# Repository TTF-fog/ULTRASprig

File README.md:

# the ULTRASprig

an updated version of the [Sprig](https://github.com/hackclub/sprig/), made to be ultra-modular and expansible!

# Why?
the current model of the sprig is a bit... outdated. It still runs on the RP2040, has only 4 (broken out) gpios and just 2Mb of flash. The ULTRASprig has 7 usable GPIOs, and a completely new expansion system that allows for up to 16MB of additional flash, + PSRAM. it also uses I2C "modules" to give even more  interfaces

## Notes:
- KiCad will throw a DRC error for the placement of the mounting headers (courtyard overlap with display), but this can be ignored safely 

# Setup
## RP2354B
- get the larger packages (the BQ, RP2354, and the TP) pre-assembled
- use a stencil to solder the smaller passives
- solder male headers into the broken out pins
## Mainboard
- Solder all components except the pinsockets
- while soldering the pinsockets, make sure to have 1mm of clearance between the tips and the SPI display
- insert the SD Card into the SPI Display
- for the battery headers, one battery header will be connected to the + and - of the battery, and the other should be connected to the battery pins of the coreboard
## Case
- the case must be printed in two parts, the front and the back
- there are 4 mounting holes in the case, which must be connected using screws to those mounting holes on the mainboard
- after that, place the backplate, ensuring that the battery pins line up with the battery hoels
# Usage
- build the firmware and flash it on the sprig

# Sub(Links)
- [Zine](Sprig_Zine.pdf)
- Mainboard
    - [Mainboard BoM](BOM.csv)
    - [Gerbers - Mainboard](gerbers.zip)
    - [Mainboard Design](Mainboard/)
- Core Board
    - [Core BoM](core_board/RP2354B/BOM.csv)
    - [Coreboard Design Files](core_board/RP2354B/)
- Expansions
    - IO Expander   
        - [Design](Expansions/IOExpander/)
        - [Gerbers](Expansions/IOExpander/Gerbers.zip)
        - [BoM](Expansions/IOExpander/BOM.csv)
    - Flash Breakout   
        - [Design](Expansions/FlashBreakout/)
        - [Gerbers](Expansions/FlashBreakout/gerbers.zip)
        - [BoM](Expansions/FlashBreakout/BOM.csv)
    - IMU Breakout   
        - [Design](Expansions/IMUBreakout/)
        - [Gerbers](Expansions/IMUBreakout/Gerbers.zip)
        - [BoM](Expansions/IMUBreakout/BOM.csv)

- [Gerbers - coreboard](core_board/RP2354B/Gerbers.zip)

# Zine

> check the pdf version too!
# Renders

> front view

> back view w/ board and battery headers

> front view, main board with modules

> a very rushed blender render rhyme

> case for the ULTRASprig

> textured preview of CAD
# Routing

> routed mainboard

> routed coreboard

# Schematics

> mainboard schematic

> coreboard schematic

> note: some of the cad model pictures are outdated, double-check the source file

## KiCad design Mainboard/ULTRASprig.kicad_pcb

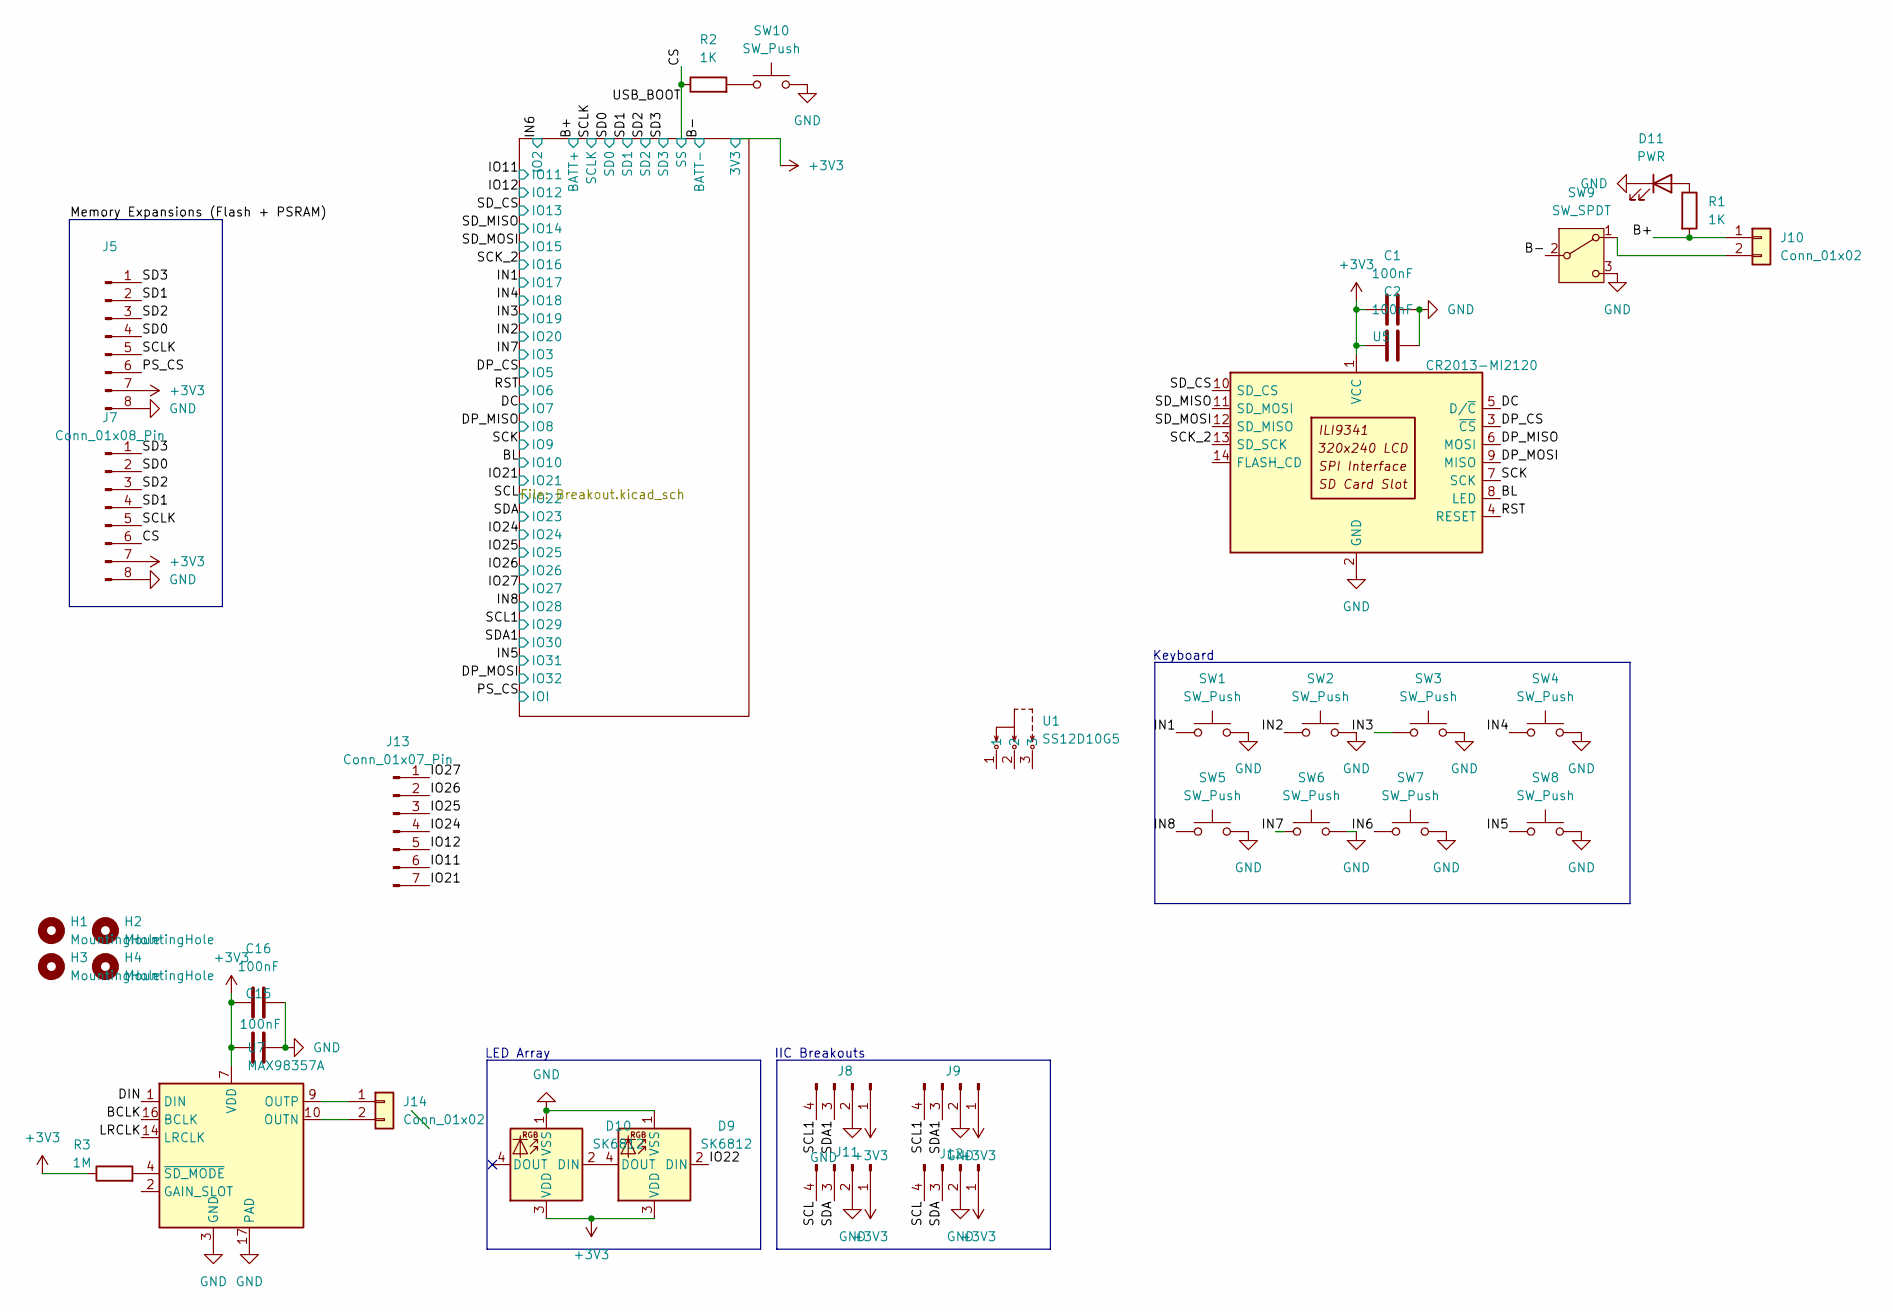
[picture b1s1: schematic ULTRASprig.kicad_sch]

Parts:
C1, C2, C15, C16: 100nF; C_0402_1005Metric
D9, D10: SK6812; LED_SK6812_PLCC4_5.0x5.0mm_P3.2mm
D11: PWR; LED_0603_1608Metric
H1, H2, H3, H4: MountingHole; MountingHole_2.2mm_M2
J5, J7: Conn_01x08_Pin; PinSocket_1x08_P2.54mm_Horizontal
J8, J9, J11, J12: Conn_01x04_Pin; PinSocket_1x04_P2.54mm_Horizontal
J10, J14: Conn_01x02; PinHeader_1x02_P2.54mm_Vertical
J13: Conn_01x07_Pin; PinSocket_1x07_P2.54mm_Vertical
R1: 1K; R_0402_1005Metric
R2: 1K; R_0603_1608Metric
R3: 1M; R_0603_1608Metric
SW1, SW2, SW3, SW4, SW5, SW6, SW7, SW8: SW_Push; SW_PUSH-12mm
SW9: SW_SPDT; SW_SPST_B3S-1100
SW10: SW_Push; SW_Push_1P1T_NO_CK_KMR2
U1: SS12D10G5; SW-TH_SHOU-HAN_SS12D10G4; MPN SS12D10G5; LCSC Part C7431054
U5: CR2013-MI2120
U7: MAX98357A; TQFN-16-1EP_3x3mm_P0.5mm_EP1.23x1.23mm

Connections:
+3V3: C1.1, C2.1, C15.2, C16.2, D9.3 (VDD), D10.3 (VDD), J5.7, J7.7, J8.1, J9.1, J11.1, J12.1, R3.1, U5.1 (VCC), U7.7 (VDD), U7.8 (VDD); also elsewhere on the board
/B+: J10.1, R1.2; also elsewhere on the board
/B-: SW9.2 (B); also elsewhere on the board
/BCLK: U7.16 (BCLK)
/BL: U5.8 (LED); also elsewhere on the board
/CS: J7.6, R2.1; also elsewhere on the board
/DC: U5.5 (D/~C); also elsewhere on the board
/DIN: U7.1 (DIN)
/DP_CS: U5.3 (~CS); also elsewhere on the board
/DP_MISO: U5.6 (MOSI); also elsewhere on the board
/DP_MOSI: U5.9 (MISO); also elsewhere on the board
/IN1: SW1.1; also elsewhere on the board
/IN2: SW2.1; also elsewhere on the board
/IN3: SW3.1; also elsewhere on the board
/IN4: SW4.1; also elsewhere on the board
/IN5: SW8.1; also elsewhere on the board
/IN6: SW7.1; also elsewhere on the board
/IN7: SW6.1; also elsewhere on the board
/IN8: SW5.1; also elsewhere on the board
/IO11: J13.6; also elsewhere on the board
/IO12: J13.5; also elsewhere on the board
/IO21: J13.7; also elsewhere on the board
/IO22: D9.2 (DIN)
/IO24: J13.4; also elsewhere on the board
/IO25: J13.3; also elsewhere on the board
/IO26: J13.2; also elsewhere on the board
/IO27: J13.1; also elsewhere on the board
/LRCLK: U7.14 (LRCLK)
/PS_CS: J5.6; also elsewhere on the board
/RST: U5.4 (RESET); also elsewhere on the board
/SCK: U5.7 (SCK); also elsewhere on the board
/SCK_2: U5.13 (SD_SCK); also elsewhere on the board
/SCL: J11.4, J12.4; also elsewhere on the board
/SCL1: J8.4, J9.4; also elsewhere on the board
/SCLK: J5.5, J7.5; also elsewhere on the board
/SD0: J5.4, J7.2; also elsewhere on the board
/SD1: J5.2, J7.4; also elsewhere on the board
/SD2: J5.3, J7.3; also elsewhere on the board
/SD3: J5.1, J7.1; also elsewhere on the board
/SDA: J11.3, J12.3; also elsewhere on the board
/SDA1: J8.3, J9.3; also elsewhere on the board
/SD_CS: U5.10 (SD_CS); also elsewhere on the board
/SD_MISO: U5.11 (SD_MOSI); also elsewhere on the board
/SD_MOSI: U5.12 (SD_MISO); also elsewhere on the board
GND: C1.2, C2.2, C15.1, C16.1, D9.1 (VSS), D10.1 (VSS), D11.1 (K), J5.8, J7.8, J8.2, J9.2, J11.2, J12.2, SW1.2, SW2.2, SW3.2, SW4.2, SW5.2, SW6.2, SW7.2, SW8.2, SW9.3 (C), SW10.2, U5.2 (GND), U7.3 (GND), U7.11 (GND), U7.15 (GND), U7.17 (PAD)
unnamed: D9.4 (DOUT), D10.2 (DIN)
unnamed: D11.2 (A), R1.1
unnamed: J10.2, SW9.1 (A)
unnamed: J14.1, U7.9 (OUTP)
unnamed: J14.2, U7.10 (OUTN)
unnamed: R2.2, SW10.1
unnamed: R3.2, U7.4 (~SD_MODE)

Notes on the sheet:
Keyboard
LED Array
IIC Breakouts

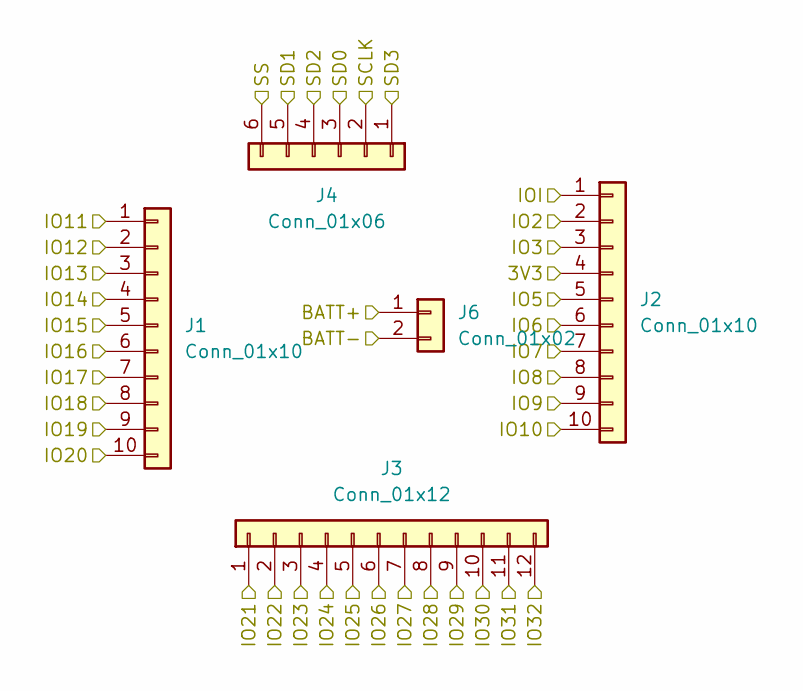
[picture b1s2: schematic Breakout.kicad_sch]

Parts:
J1, J2: Conn_01x10; PinSocket_1x10_P2.54mm_Vertical
J3: Conn_01x12; PinSocket_1x12_P2.54mm_Vertical
J4: Conn_01x06; PinSocket_1x06_P2.54mm_Vertical
J6: Conn_01x02; PinHeader_1x02_P2.54mm_Vertical

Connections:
+3V3: J2.4; also elsewhere on the board
/B+: J6.1; also elsewhere on the board
/B-: J6.2; also elsewhere on the board
/BL: J2.10; also elsewhere on the board
/CS: J4.6; also elsewhere on the board
/DC: J2.7; also elsewhere on the board
/DP_CS: J2.5; also elsewhere on the board
/DP_MISO: J2.8; also elsewhere on the board
/DP_MOSI: J3.12; also elsewhere on the board
/IN1: J1.7; also elsewhere on the board
/IN2: J1.10; also elsewhere on the board
/IN3: J1.9; also elsewhere on the board
/IN4: J1.8; also elsewhere on the board
/IN5: J3.11; also elsewhere on the board
/IN6: J2.2; also elsewhere on the board
/IN7: J2.3; also elsewhere on the board
/IN8: J3.8; also elsewhere on the board
/IO11: J1.1; also elsewhere on the board
/IO12: J1.2; also elsewhere on the board
/IO21: J3.1; also elsewhere on the board
/IO24: J3.4; also elsewhere on the board
/IO25: J3.5; also elsewhere on the board
/IO26: J3.6; also elsewhere on the board
/IO27: J3.7; also elsewhere on the board
/PS_CS: J2.1; also elsewhere on the board
/RST: J2.6; also elsewhere on the board
/SCK: J2.9; also elsewhere on the board
/SCK_2: J1.6; also elsewhere on the board
/SCL: J3.2; also elsewhere on the board
/SCL1: J3.9; also elsewhere on the board
/SCLK: J4.2; also elsewhere on the board
/SD0: J4.3; also elsewhere on the board
/SD1: J4.5; also elsewhere on the board
/SD2: J4.4; also elsewhere on the board
/SD3: J4.1; also elsewhere on the board
/SDA: J3.3; also elsewhere on the board
/SDA1: J3.10; also elsewhere on the board
/SD_CS: J1.3; also elsewhere on the board
/SD_MISO: J1.4; also elsewhere on the board
/SD_MOSI: J1.5; also elsewhere on the board

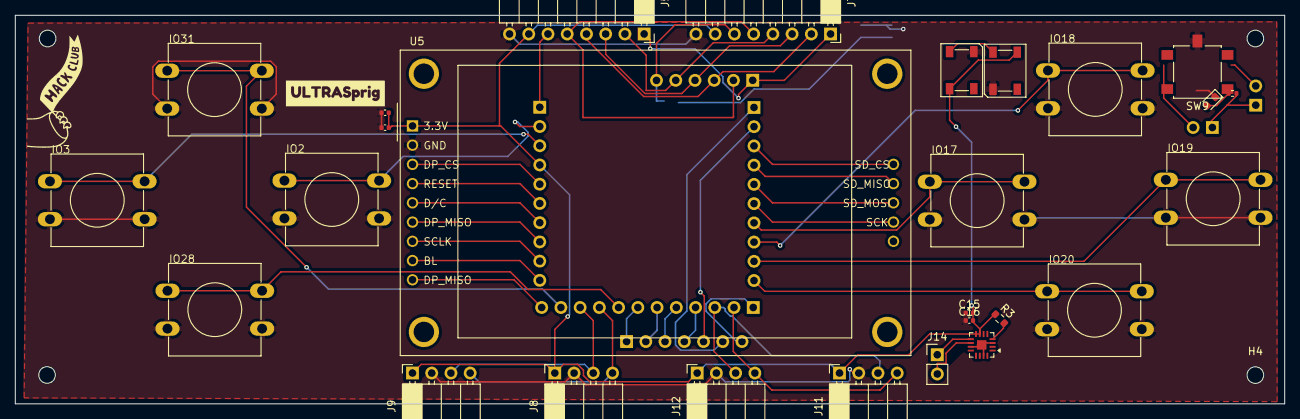
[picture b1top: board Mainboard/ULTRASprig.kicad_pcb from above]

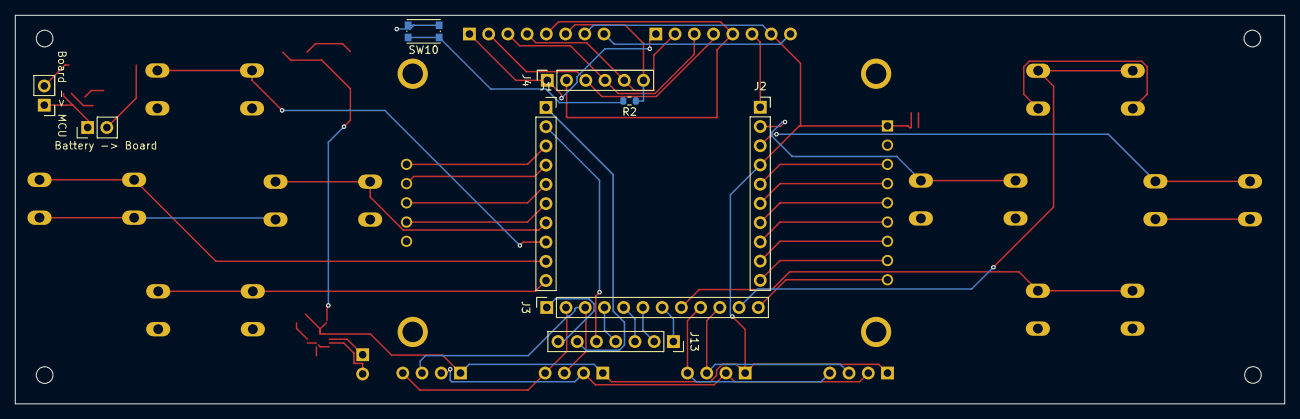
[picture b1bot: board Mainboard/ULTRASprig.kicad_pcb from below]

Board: 2 copper layers, 167.6 x 51.3 mm, 41 parts (9 on the bottom side), 48 nets.

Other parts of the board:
kibuzzard-6A30251C: G***; kibuzzard-6A30251C

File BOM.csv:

Comment,Designator,Footprint,LCSC,Quantity,URL, Unit Price,Price
100nF,"C1,C15,C16,C2",C_0402_1005Metric,C1525,4,https://www.lcsc.com/product-detail/C1525.html ,0.0031,0.31
1K,R1,R_0402_1005Metric,C11702,1,https://www.lcsc.com/product-detail/C11702.html ,0.0011,0.011
1K,R2,R_0603_1608Metric,C21190,1,https://www.lcsc.com/product-detail/C21190.html ,0.0017,0.017
1M,R3,R_0603_1608Metric,C22935,1,https://www.lcsc.com/product-detail/C22935.html,0.0018,0.18
Conn_01x02,"J10,J6",PinHeader_1x02_P2.54mm_Vertical,C492401,2,https://www.lcsc.com/product-detail/C492401.html,0.0161,0.81
Conn_01x04_Pin,"J11,J12,J8,J9",PinSocket_1x04_P2.54mm_Horizontal,C2718488,4,https://www.lcsc.com/product-detail/C2718488.html,0.0786,0.79
Conn_01x06,J4,PinSocket_1x06_P2.54mm_Vertical,C7499363,1,https://www.lcsc.com/product-detail/C7499363.html,0.1286,0.64
Conn_01x07_Pin,J13,PinSocket_1x07_P2.54mm_Vertical,C5371993,1,https://www.lcsc.com/product-detail/C5371993.html,0.0963,0.48
Conn_01x08_Pin,"J5,J7",PinSocket_1x08_P2.54mm_Horizontal,C7499328,2,https://www.lcsc.com/product-detail/C7499328.html,0.1351,0.68
Conn_01x10,"J1,J2",PinSocket_1x10_P2.54mm_Vertical,C2925557,2,https://www.lcsc.com/product-detail/C2925557.html,0.1279,0.64
Conn_01x12,J3,PinSocket_1x12_P2.54mm_Vertical,C492401,1,https://www.lcsc.com/product-detail/C492401.html,0.0161,0.81
MAX98357A,U7,TQFN-16-1EP_3x3mm_P0.5mm_EP1.23x1.23mm,C910544,1,https://www.lcsc.com/product-detail/C910544.html,1.3362,1.34
PWR,D11,LED_0603_1608Metric,C2286,1,https://www.lcsc.com/product-detail/C2286.html,0.0073,0.73
SK6812,"D10,D9",LED_SK6812_PLCC4_5.0x5.0mm_P3.2mm,C5378734,2,https://www.lcsc.com/product-detail/C5378734.html,0.1656,0.83
SW_Push,"SW1,SW10,SW2,SW3,SW4,SW5,SW6,SW7,SW8",SW_PUSH-12mm,C963201,9,https://www.lcsc.com/product-detail/C963201.html,0.216,1.08
SW_SPDT,SW9,SW_SPST_B3S-1100,C7421519,1,https://www.lcsc.com/product-detail/C7421519.html,0.444,0.44
CR2013-MI2120,U5,CR2013-MI2120,N/A,1,https://robu.in/product/2-8-inch-lcm-tft-color-screen-ili934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,9.4,9.41
PCB Milling,N/A,N/A,N/A,,https://jlcpcb.com,7.7,7.7
,,,,,,19.8755,26.898

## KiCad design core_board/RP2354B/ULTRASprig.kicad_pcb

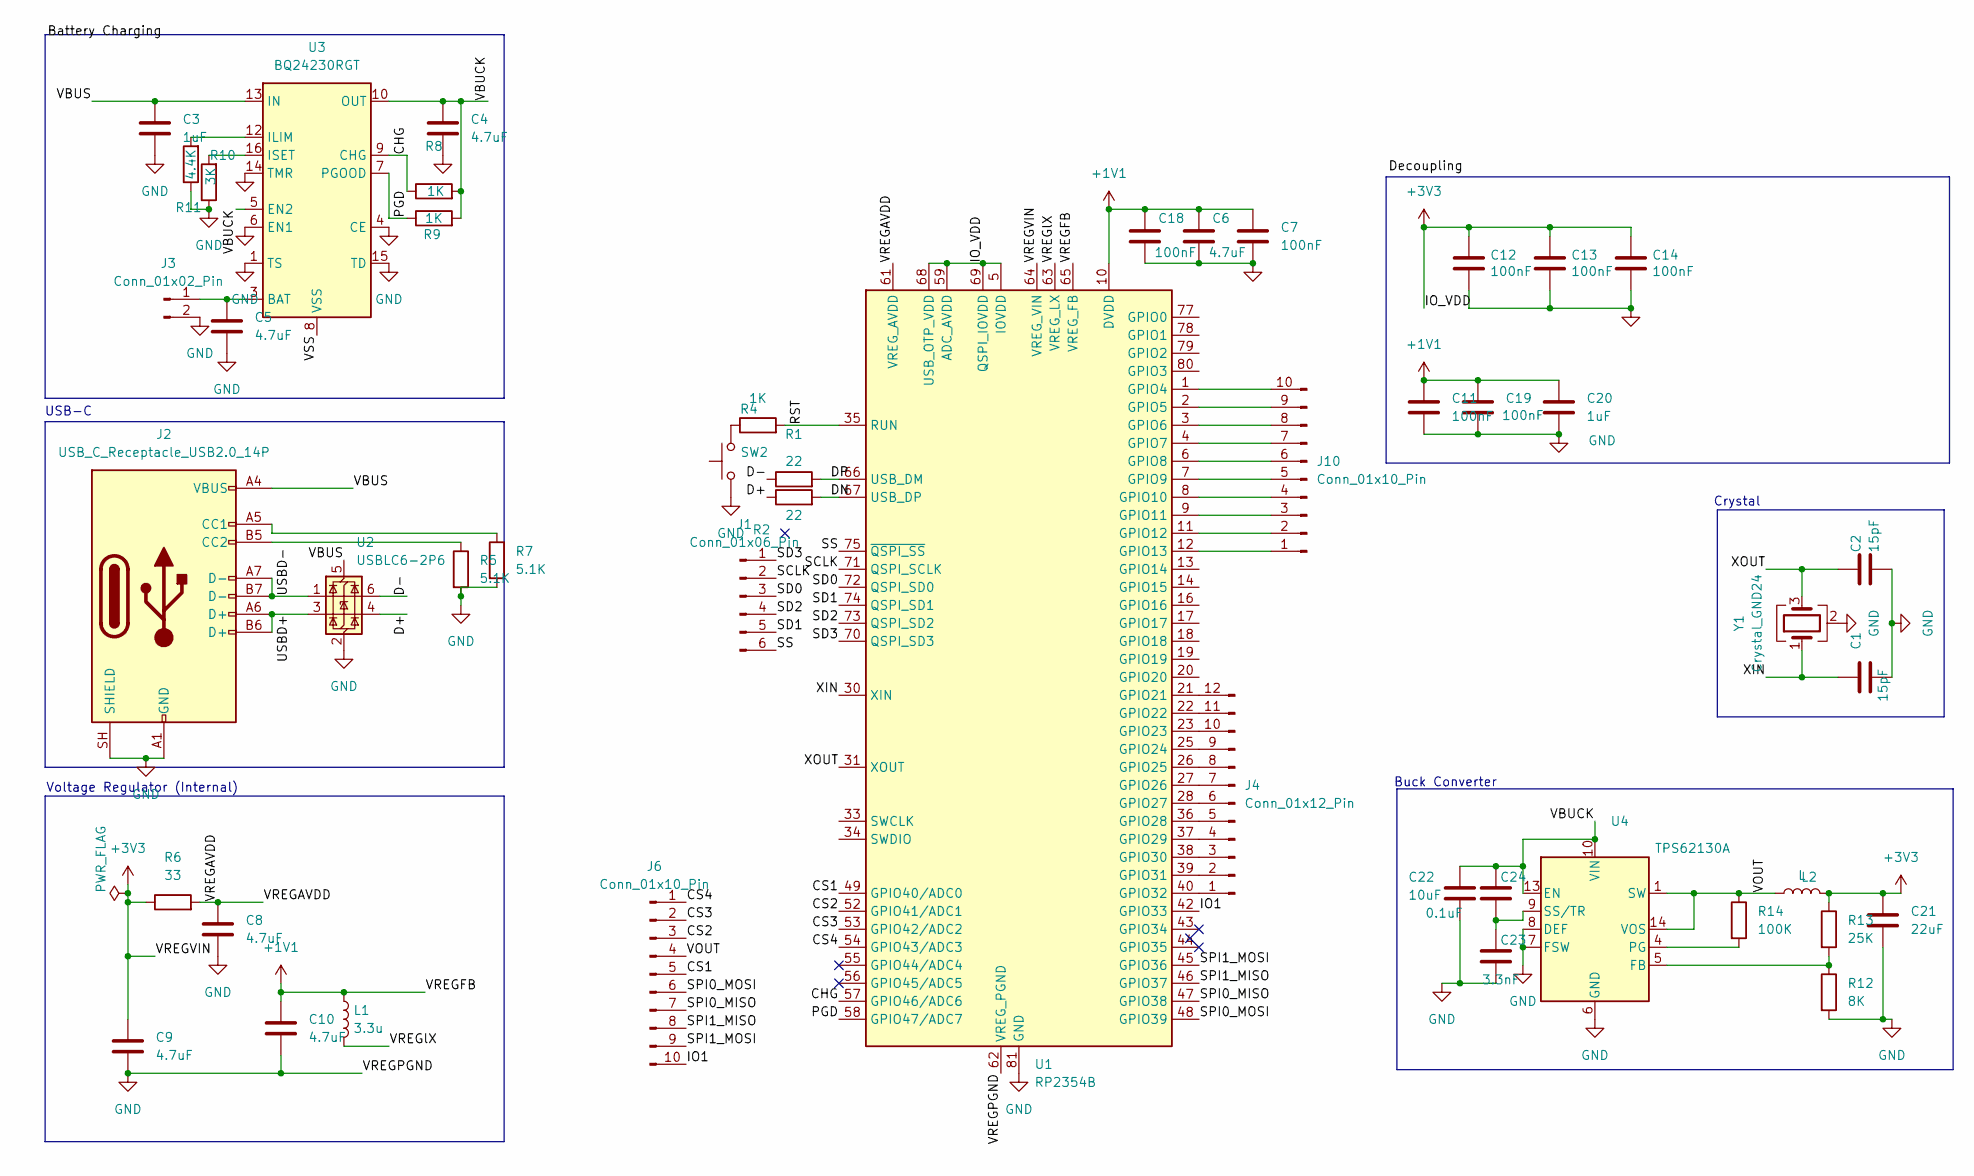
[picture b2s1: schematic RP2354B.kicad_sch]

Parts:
C1, C2: 15pF; C_0402_1005Metric
C3, C20: 1uF; C_0402_1005Metric
C4, C5, C6, C8, C9, C10: 4.7uF; C_0402_1005Metric
C7, C11, C12, C13, C14, C18, C19: 100nF; C_0402_1005Metric
C21: 22uF; C_0402_1005Metric
C22: 10uF; C_0402_1005Metric
C23: 3.3nF; C_0402_1005Metric
C24: 0.1uF; C_0402_1005Metric
J1: Conn_01x06_Pin; PinHeader_1x06_P2.54mm_Vertical
J2: USB_C_Receptacle_USB2.0_14P; USB_C_Receptacle_HRO_TYPE-C-31-M-12
J3: Conn_01x02_Pin; PinHeader_1x02_P2.54mm_Vertical
J4: Conn_01x12_Pin; PinSocket_1x12_P2.54mm_Vertical
J6, J10: Conn_01x10_Pin; PinHeader_1x10_P2.54mm_Vertical
L1: 3.3u; L_0402_1005Metric
L2: L; L_0402_1005Metric
R1, R2: 22; R_0402_1005Metric
R4, R8, R9: 1K; R_0402_1005Metric
R5, R7: 5.1K; R_0402_1005Metric
R6: 33; R_0402_1005Metric
R10: 3K; R_0402_1005Metric
R11: 4.4K; R_0402_1005Metric
R12: 8K; R_0402_1005Metric
R13: 25K; R_0603_1608Metric
R14: 100K; R_0402_1005Metric
SW2: SW_Push
U1: RP2354B; QFN-80-1EP_10x10mm_P0.4mm_EP3.4x3.4mm
U2: USBLC6-2P6; SOT-666
U3: BQ24230RGT; VQFN-16-1EP_3x3mm_P0.5mm_EP1.68x1.68mm_ThermalVias
U4: TPS62130A; VQFN-16-1EP_3x3mm_P0.5mm_EP1.68x1.68mm_ThermalVias
Y1: Crystal_GND24; Crystal_SMD_3225-4Pin_3.2x2.5mm

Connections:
+1V1: C6.1, C7.1, C10.1, C11.1, C18.1, C19.1, C20.1, L1.1, U1.10 (DVDD), U1.32 (DVDD), U1.51 (DVDD), U1.65 (VREG_FB)
+3V3: C9.1, C12.1, C13.1, C14.1, C21.1, L2.2, R6.1, R13.1, U1.5 (IOVDD), U1.15 (IOVDD), U1.24 (IOVDD), U1.29 (IOVDD), U1.41 (IOVDD), U1.50 (IOVDD), U1.59 (ADC_AVDD), U1.60 (IOVDD), U1.64 (VREG_VIN), U1.68 (USB_OTP_VDD), U1.69 (QSPI_IOVDD), U1.76 (IOVDD)
/RP2354 Board/CHG: R8.1, U1.57 (GPIO46/ADC6), U3.9 (CHG)
/RP2354 Board/CS1: J6.5, U1.49 (GPIO40/ADC0)
/RP2354 Board/CS2: J6.3, U1.52 (GPIO41/ADC1)
/RP2354 Board/CS3: J6.2, U1.53 (GPIO42/ADC2)
/RP2354 Board/CS4: J6.1, U1.54 (GPIO43/ADC3)
/RP2354 Board/D+: R2.1, U2.4 (I/O2)
/RP2354 Board/D-: R1.1, U2.6 (I/O1)
/RP2354 Board/DN: R2.2, U1.67 (USB_DP)
/RP2354 Board/DP: R1.2, U1.66 (USB_DM)
/RP2354 Board/IO1: J6.10, U1.42 (GPIO33)
/RP2354 Board/PGD: R9.1, U1.58 (GPIO47/ADC7), U3.7 (PGOOD)
/RP2354 Board/RST: R4.2, U1.35 (RUN)
/RP2354 Board/SCLK: J1.2, U1.71 (QSPI_SCLK)
/RP2354 Board/SD0: J1.3, U1.72 (QSPI_SD0)
/RP2354 Board/SD1: J1.5, U1.74 (QSPI_SD1)
/RP2354 Board/SD2: J1.4, U1.73 (QSPI_SD2)
/RP2354 Board/SD3: J1.1, U1.70 (QSPI_SD3)
/RP2354 Board/SPI0_MISO: J6.7, U1.47 (GPIO38)
/RP2354 Board/SPI0_MOSI: J6.6, U1.48 (GPIO39)
/RP2354 Board/SPI1_MISO: J6.8, U1.46 (GPIO37)
/RP2354 Board/SPI1_MOSI: J6.9, U1.45 (GPIO36)
/RP2354 Board/SS: J1.6, U1.75 (~QSPI_SS)
/RP2354 Board/USBD+: J2.A6 (D+), J2.B6 (D+), U2.3 (I/O2)
/RP2354 Board/USBD-: J2.A7 (D-), J2.B7 (D-), U2.1 (I/O1)
/RP2354 Board/VBUCK: C4.1, C22.1, C24.1, R8.2, R9.2, U3.5 (EN2), U3.10 (OUT), U3.11 (OUT), U4.10 (VIN), U4.11 (VIN), U4.12 (VIN), U4.13 (EN)
/RP2354 Board/VBUS: C3.1, J2.A4 (VBUS), J2.A9 (VBUS), J2.B4 (VBUS), J2.B9 (VBUS), U2.5 (VBUS), U3.13 (IN)
/RP2354 Board/VOUT: J6.4, L2.1, R14.1, U4.1 (SW), U4.2 (SW), U4.3 (SW), U4.14 (VOS)
/RP2354 Board/VREGAVDD: C8.1, R6.2, U1.61 (VREG_AVDD)
/RP2354 Board/VREGlX: L1.2, U1.63 (VREG_LX)
/RP2354 Board/VSS: U3.8 (VSS), U3.17 (VSS)
/RP2354 Board/XIN: C1.1, U1.30 (XIN), Y1.1
/RP2354 Board/XOUT: C2.1, U1.31 (XOUT), Y1.3
GND: C1.2, C2.2, C3.2, C4.2, C5.2, C6.2, C7.2, C8.2, C9.2, C10.2, C11.2, C12.2, C13.2, C14.2, C18.2, C19.2, C20.2, C21.2, C22.2, C23.2, J2.A1 (GND), J2.A12 (GND), J2.B1 (GND), J2.B12 (GND), J2.SH (SHIELD), J3.2, R5.2, R7.2, R10.1, R11.1, R12.2, SW2.1, U1.62 (VREG_PGND), U1.81 (GND), U2.2 (GND), U3.1 (TS), U3.4 (CE), U3.6 (EN1), U3.14 (TMR), U3.15 (TD), U4.6 (GND), U4.7 (FSW), U4.8 (DEF), U4.15 (GND), U4.16 (GND), U4.17 (GND), Y1.2 (G), Y1.4 (G)
unnamed: J2.A5 (CC1), R7.1
unnamed: J2.B5 (CC2), R5.1
unnamed: C5.1, J3.1, U3.2 (BAT), U3.3 (BAT)
unnamed: J4.1, U1.40 (GPIO32)
unnamed: J4.2, U1.39 (GPIO31)
unnamed: J4.3, U1.38 (GPIO30)
unnamed: J4.4, U1.37 (GPIO29)
unnamed: J4.5, U1.36 (GPIO28)
unnamed: J4.6, U1.28 (GPIO27)
unnamed: J4.7, U1.27 (GPIO26)
unnamed: J4.8, U1.26 (GPIO25)
unnamed: J4.9, U1.25 (GPIO24)
unnamed: J4.10, U1.23 (GPIO23)
unnamed: J4.11, U1.22 (GPIO22)
unnamed: J4.12, U1.21 (GPIO21)
unnamed: J10.1, U1.12 (GPIO13)
unnamed: J10.2, U1.11 (GPIO12)
unnamed: J10.3, U1.9 (GPIO11)
unnamed: J10.4, U1.8 (GPIO10)
unnamed: J10.5, U1.7 (GPIO9)
unnamed: J10.6, U1.6 (GPIO8)
unnamed: J10.7, U1.4 (GPIO7)
unnamed: J10.8, U1.3 (GPIO6)
unnamed: J10.9, U1.2 (GPIO5)
unnamed: J10.10, U1.1 (GPIO4)
unnamed: R4.1, SW2.2
unnamed: R10.2, U3.12 (ILIM)
unnamed: R11.2, U3.16 (ISET)
unnamed: R12.1, R13.2, U4.5 (FB)
unnamed: R14.2, U4.4 (PG)
unnamed: C23.1, C24.2, U4.9 (SS/TR)

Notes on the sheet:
Voltage Regulator (Internal)
USB-C
Buck Converter
Crystal

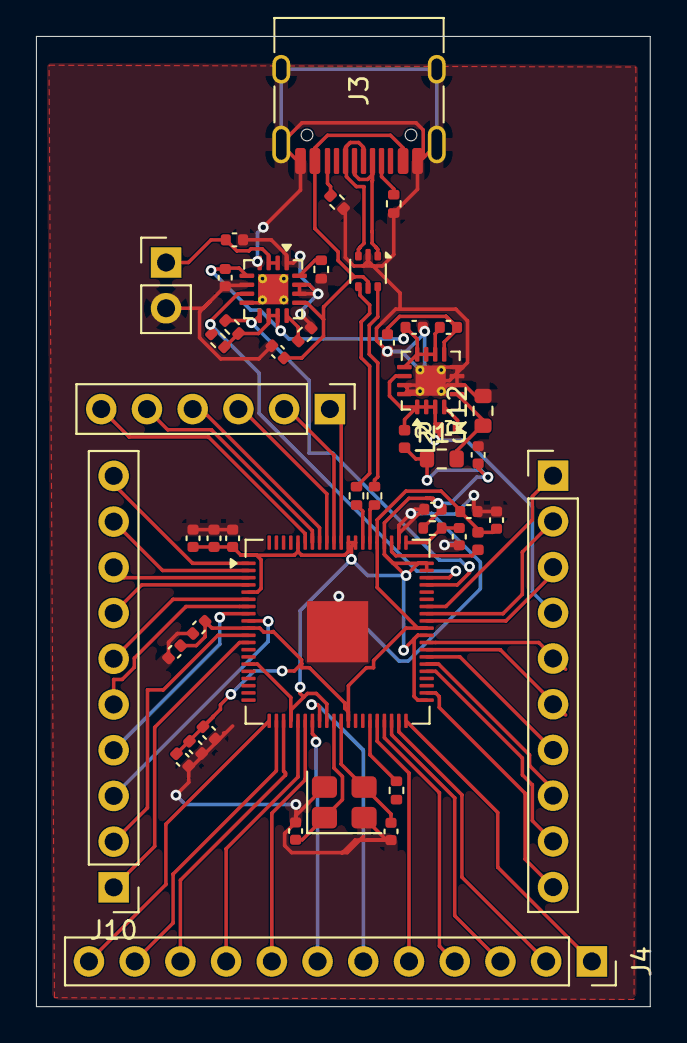
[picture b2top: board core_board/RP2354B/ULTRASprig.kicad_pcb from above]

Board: 2 copper layers, 34.1 x 53.9 mm, 47 parts (0 on the bottom side), 65 nets.

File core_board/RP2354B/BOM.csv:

Comment,Designator,Footprint,LCSC,Quantity,Link, ,Unit Price,Total Price
0.1uF,C24,C_0402_1005Metric,C15195,1,https://www.lcsc.com/product-detail/C15195.html,,0.0025,0.025
100K,R14,R_0402_1005Metric,C25741,1,https://www.lcsc.com/product-detail/C25741.html,,"$ 0.0011
",0.11
100nF,"C11,C12,C13,C14,C18,C19,C7",C_0402_1005Metric,C1525,7,https://www.lcsc.com/product-detail/C1525.html,,0.0031,0.031
10uF,C22,C_0402_1005Metric,C15525,1,https://www.lcsc.com/product-detail/C15525.html,,0.0199,1.99
15pF,"C1,C2",C_0402_1005Metric,C1548,2,https://www.lcsc.com/product-detail/C1548.html,,0.0022,0.22
1K,"R4,R8,R9",R_0402_1005Metric,C11702,3,https://www.lcsc.com/product-detail/C11702.html,,0.0011,0.11
1uF,"C20,C3",C_0402_1005Metric,C52923,2,https://www.lcsc.com/product-detail/C52923.html,,0.0143,0.72
22,"R1,R2",R_0402_1005Metric,C25092,2,https://www.lcsc.com/product-detail/C25092.html,,0.0009,0.09
22uF,C21,C_0402_1005Metric,C105226,1,https://www.lcsc.com/product-detail/C105226.html,,0.075,0.38
25K,R13,R_0603_1608Metric,C2828637,1,https://www.lcsc.com/product-detail/C2828637.html,,0.035,0.7
3.3nF,C23,C_0402_1005Metric,C26404,1,https://www.lcsc.com/product-detail/C26404.html,,0.006,0.12
3.3u,L1,L_0402_1005Metric,C48946153,1,https://www.lcsc.com/product-detail/C48946153.html,,0.0425,0.43
33,R6,R_0402_1005Metric,C25105,1,https://www.lcsc.com/product-detail/C25105.html,,0.001,0.1
3K,R10,R_0402_1005Metric,C25559,1,https://www.lcsc.com/product-detail/C25559.html,,0.0007,0.07
4.4K,R11,R_0402_1005Metric,C2088643,1,https://www.lcsc.com/product-detail/C2088643.html,,0.3144,0.31
4.7uF,"C10,C4,C5,C6,C8,C9",C_0402_1005Metric,C23733,6,https://www.lcsc.com/product-detail/C23733.html,,0.0192,0.96
5.1K,"R5,R7",R_0402_1005Metric,C25905,2,https://www.lcsc.com/product-detail/C25905.html,,0.0009,0.09
8K,R12,R_0603_1608Metric,C2924154,1,https://www.lcsc.com/product-detail/C2924154.html,,0.0142,0.71
BQ24230RGT,U3,VQFN-16-1EP_3x3mm_P0.5mm_EP1.68x1.68mm_ThermalVias,C138361,1,https://www.lcsc.com/product-detail/C138361.html,,2.2652,2.27
Conn_01x02_Pin,J3,PinHeader_1x02_P2.54mm_Vertical,C52016390,1,https://www.lcsc.com/product-detail/C52016390.html,,0.013,0.65
Conn_01x06_Pin,J1,PinHeader_1x06_P2.54mm_Vertical,C293309,1,https://www.lcsc.com/product-detail/C293309.html,,1.1299,1.13
Conn_01x10_Pin,"J10,J6",PinHeader_1x10_P2.54mm_Vertical,C2925557,2,https://www.lcsc.com/product-detail/C2925557.html,,0.1279,0.64
Conn_01x12_Pin,J4,PinSocket_1x12_P2.54mm_Vertical,C293309,1,https://www.lcsc.com/product-detail/C293309.html,,1.1299,1.13
Crystal_GND24,Y1,Crystal_SMD_3225-4Pin_3.2x2.5mm,C20625731,1,https://www.lcsc.com/product-detail/C20625731.html,,0.2956,1.48
L,L2,L_0402_1005Metric,C49067,1,https://www.lcsc.com/product-detail/C383389.html,,0.0564,0.56
RP2354B,U1,QFN-80-1EP_10x10mm_P0.4mm_EP3.4x3.4mm,C39843328,1,https://www.lcsc.com/product-detail/C39843328.html,,1.5739,1.57
TPS62130A,U4,VQFN-16-1EP_3x3mm_P0.5mm_EP1.68x1.68mm_ThermalVias,C2070623,1,https://www.lcsc.com/product-detail/C2070623.html,,1.3236,1.32
USBLC6-2P6,U2,SOT-666,C53059594,1,https://www.lcsc.com/product-detail/C53059594.html,,0.08,0.4
USB_C_Receptacle_USB2.0_14P,J2,USB_C_Receptacle_HRO_TYPE-C-31-M-12,C165948,1,https://www.lcsc.com/product-detail/C165948.html,,0.1857,0.93
PCB Milling,N/A,N/A,N/A,1,https://jlcpcb.com,,5.31,5.31
,,,,,,,14.044,24.556

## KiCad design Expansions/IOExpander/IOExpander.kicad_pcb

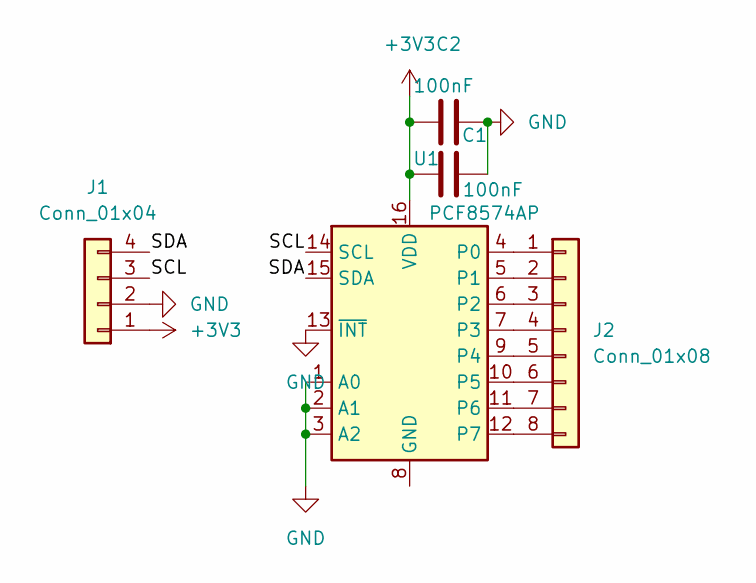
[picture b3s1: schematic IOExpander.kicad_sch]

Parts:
C1, C2: 100nF; C_0603_1608Metric
J1: Conn_01x04; PinHeader_1x04_P2.54mm_Horizontal
J2: Conn_01x08; PinHeader_1x09_P2.54mm_Horizontal
U1: PCF8574AP; DIP-16_W7.62mm

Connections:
+3V3: C1.2, C2.2, J1.1, U1.16 (VDD)
/SCL: J1.3, U1.14 (SCL)
/SDA: J1.4, U1.15 (SDA)
GND: C1.1, C2.1, J1.2, U1.1 (A0), U1.2 (A1), U1.3 (A2), U1.13 (~INT)
unnamed: J2.1, U1.4 (P0)
unnamed: J2.2, U1.5 (P1)
unnamed: J2.3, U1.6 (P2)
unnamed: J2.4, U1.7 (P3)
unnamed: J2.5, U1.9 (P4)
unnamed: J2.6, U1.10 (P5)
unnamed: J2.7, U1.11 (P6)
unnamed: J2.8, U1.12 (P7)

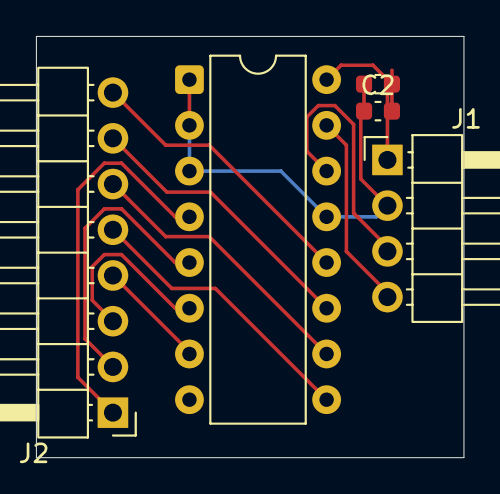
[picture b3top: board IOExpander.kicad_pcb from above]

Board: 2 copper layers, 23.8 x 23.4 mm, 5 parts (0 on the bottom side), 12 nets.

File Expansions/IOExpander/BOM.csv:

Comment,Designator,Footprint,LCSC,Quantity,Link,Unit Price,Total Price
100nF,"C1,C2",C_0603_1608Metric,C14663,2,https://www.lcsc.com/product-detail/C14663.html,0.0172,1.72
Conn_01x04,J1,PinHeader_1x04_P2.54mm_Horizontal,C52016392,1,https://www.lcsc.com/product-detail/C52016392.html,0.0283,0.57
PCF8574AP,U1,DIP-16_W7.62mm,C398072,1,https://www.lcsc.com/product-detail/C398072.html,0.79,0.79
Conn_01x08,J2,PinHeader_1x08_P2.54mm_Horizontal,C20607071,1,https://www.lcsc.com/product-detail/C20607071.html,0.0958,0.48
PCB Milling,n/a,n/a,n/a,1,https://jlcpcb.com,2.2,2.2
,,,,,,3.1313,5.76

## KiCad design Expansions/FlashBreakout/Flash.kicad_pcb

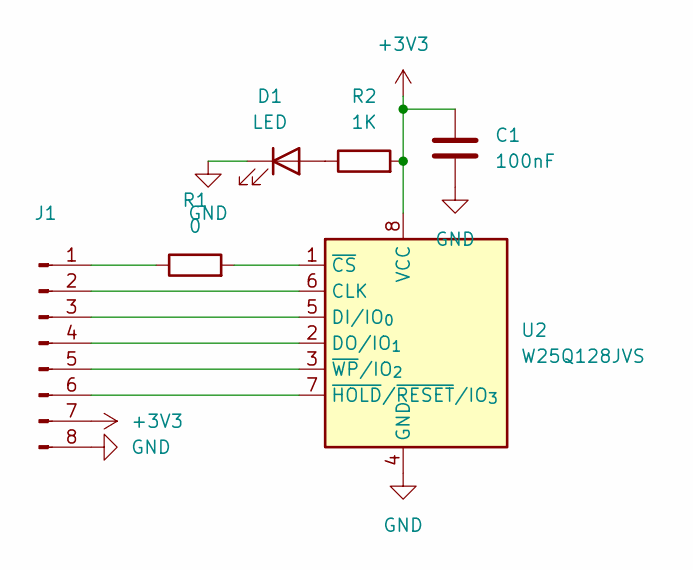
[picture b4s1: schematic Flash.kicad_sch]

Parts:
C1: 100nF; C_0402_1005Metric
D1: LED; LED_0603_1608Metric
J1: Conn_01x08_Pin; PinHeader_1x08_P2.54mm_Horizontal
R1: 0; R_0402_1005Metric
R2: 1K; R_0402_1005Metric
U2: W25Q128JVS; SOIC-8_5.3x5.3mm_P1.27mm

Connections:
+3V3: C1.1, J1.7, R2.2, U2.8 (VCC)
GND: C1.2, D1.1 (K), J1.8, U2.4 (GND)
unnamed: D1.2 (A), R2.1
unnamed: J1.1, R1.1
unnamed: J1.2, U2.6 (CLK)
unnamed: J1.3, U2.5 (DI/IO_{0})
unnamed: J1.4, U2.2 (DO/IO_{1})
unnamed: J1.5, U2.3 (~WP/IO_{2})
unnamed: J1.6, U2.7 (~HOLD/~RESET/IO_{3})
unnamed: R1.2, U2.1 (~CS)

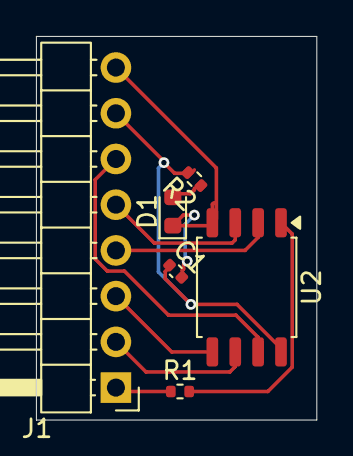
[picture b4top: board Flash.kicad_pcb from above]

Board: 2 copper layers, 15.6 x 21.3 mm, 6 parts (0 on the bottom side), 10 nets.

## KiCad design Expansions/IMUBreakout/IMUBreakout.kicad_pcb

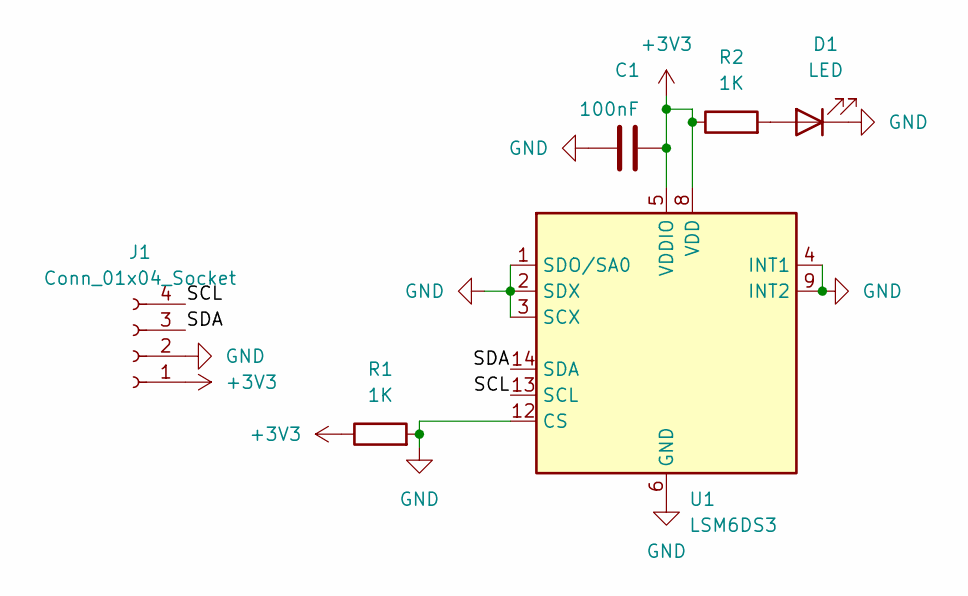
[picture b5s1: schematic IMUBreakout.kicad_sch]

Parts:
C1: 100nF; C_0402_1005Metric
D1: LED; LED_0603_1608Metric
J1: Conn_01x04_Socket; PinHeader_1x04_P2.54mm_Horizontal
R1, R2: 1K; R_0402_1005Metric
U1: LSM6DS3; LGA-14_3x2.5mm_P0.5mm_LayoutBorder3x4y

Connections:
+3V3: C1.1, J1.1, R1.1, R2.1, U1.5 (VDDIO), U1.8 (VDD)
/SCL: J1.4, U1.13 (SCL)
/SDA: J1.3, U1.14 (SDA)
GND: C1.2, D1.1 (K), J1.2, R1.2, U1.1 (SDO/SA0), U1.2 (SDX), U1.3 (SCX), U1.4 (INT1), U1.6 (GND), U1.7 (GND), U1.9 (INT2), U1.12 (CS)
unnamed: D1.2 (A), R2.2

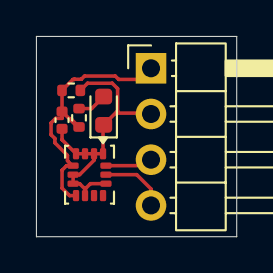
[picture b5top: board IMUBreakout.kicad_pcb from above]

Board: 2 copper layers, 11.1 x 11.1 mm, 6 parts (0 on the bottom side), 5 nets.

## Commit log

2026-06-16 add gerbers
2026-06-16 remove extra files
2026-06-18 add expansion modules
2026-06-19 more stuff
2026-06-19 add RP2354 BoM
2026-06-19 add links, total price to BoM
2026-06-19 final readme
2026-06-19 add zine, expand quick-links
2026-06-19 sliught formatting update
2026-06-19 bingus
2026-06-19 reformat, cleanup structure
2026-06-19 change links, clarification
2026-06-20 add firmware, CAD, buh
2026-06-20 weesa doneas
2026-06-20 add sprig submodule
2026-06-20 fix broken sublinsk
2026-06-20 idk boss
2026-06-20 update stupid nbs
2026-06-20 new zine
